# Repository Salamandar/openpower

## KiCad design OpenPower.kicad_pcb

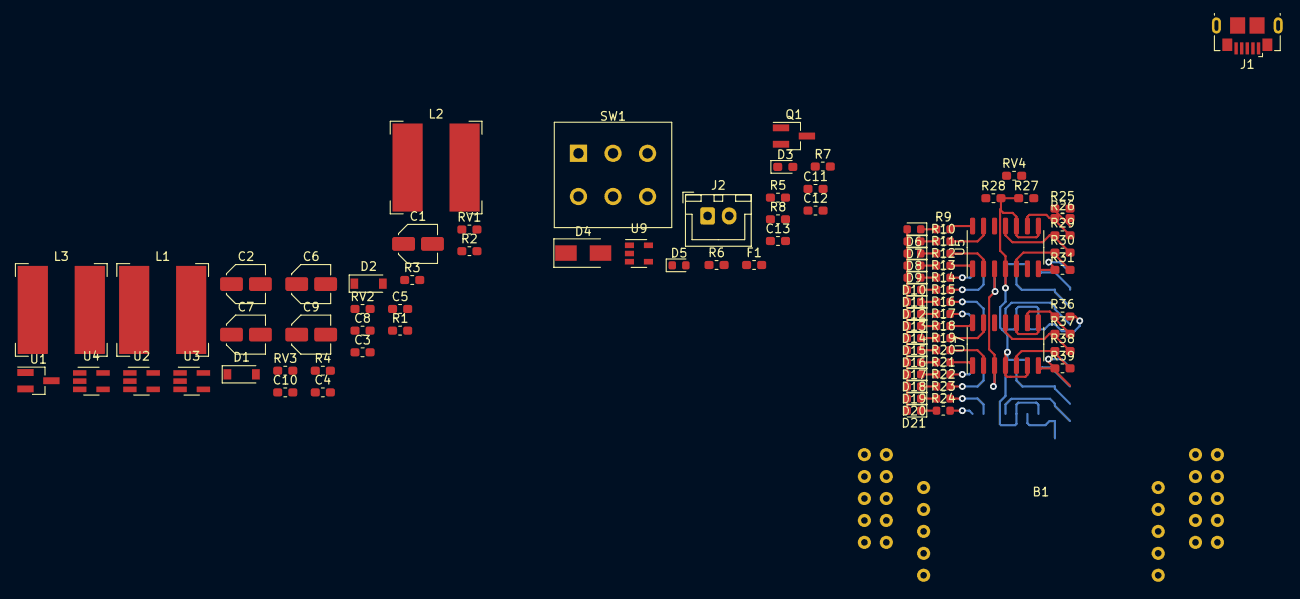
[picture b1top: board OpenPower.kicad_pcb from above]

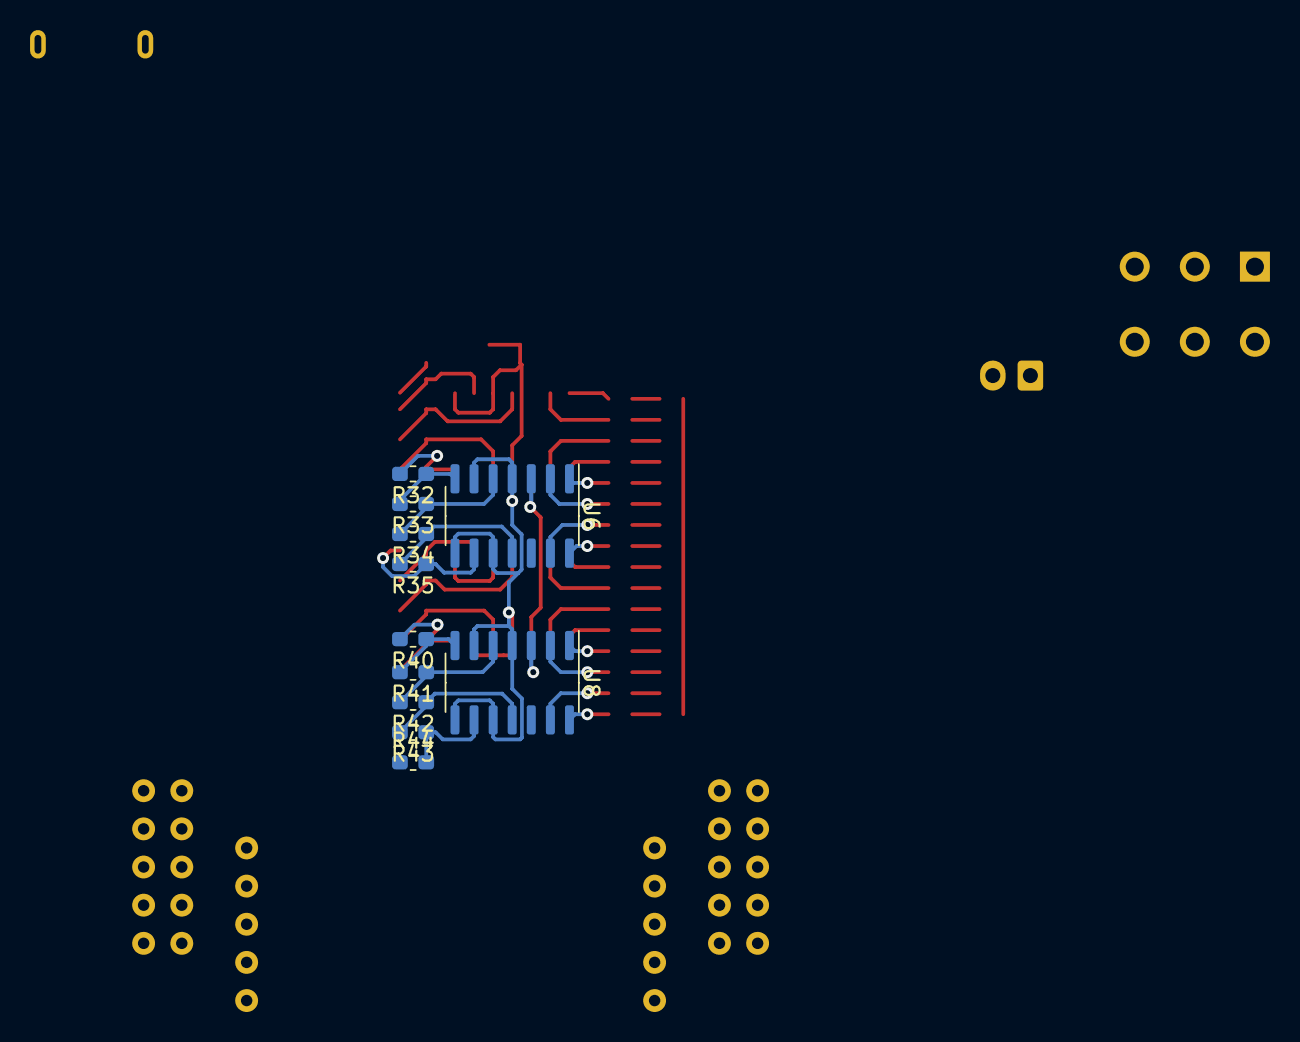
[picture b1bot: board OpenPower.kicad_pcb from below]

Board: 2 copper layers, 100 parts (11 on the bottom side), 69 nets.

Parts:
B1: breadboard
C1, C2, C6, C7: 22u; C_Elec_4x5.8
C3, C4, C8, C13: 1u; C_0603_1608Metric_Pad1.05x0.95mm_HandSolder
C5: 5.6u; C_0603_1608Metric_Pad1.05x0.95mm_HandSolder
C9: 100u; C_Elec_4x5.8
C10: 2u2; C_0603_1608Metric_Pad1.05x0.95mm_HandSolder
C11, C12: 4u7; C_0603_1608Metric_Pad1.05x0.95mm_HandSolder
D1, D2: D_Schottky; D_SOD-123
D3: LED; LED_0603_1608Metric_Pad1.05x0.95mm_HandSolder
D4: B130LAW; D_SMA
D5, D6, D7, D8, D9, D10, D11, D12, D13, D14, D15, D16, D17, D18, D19, D20, D21: LED; LED_0603_1608Metric
F1: Fuse; Fuse_0603_1608Metric_Pad1.05x0.95mm_HandSolder
J1: USB_B_Micro; USB_Micro-B_GCT_USB3076-30-A
J2: Battery; JST_XH_B2B-XH-A_1x02_P2.50mm_Vertical
L1, L2, L3: 22uH; L_Bourns-SRN1060
Q1: PMOS; SOT-23_Handsoldering
R1, R7: 100k; R_0603_1608Metric_Pad1.05x0.95mm_HandSolder
R2, R25: 12k; R_0603_1608Metric_Pad1.05x0.95mm_HandSolder
R3: 82k; R_0603_1608Metric_Pad1.05x0.95mm_HandSolder
R4: 2k2; R_0603_1608Metric_Pad1.05x0.95mm_HandSolder
R5, R27, R28, R29, R30, R31, R32, R33, R34, R35, R36, R40: 10k; R_0603_1608Metric_Pad1.05x0.95mm_HandSolder
R6, R8: 470; R_0603_1608Metric_Pad1.05x0.95mm_HandSolder
R9, R10, R11, R12, R13, R14, R15, R16, R17, R18, R19, R20, R21, R22, R23, R24: 1k; R_0603_1608Metric
R26: 1k; R_0603_1608Metric_Pad1.05x0.95mm_HandSolder
R37, R43: 4k; R_0603_1608Metric_Pad1.05x0.95mm_HandSolder
R38, R39: 3k; R_0603_1608Metric_Pad1.05x0.95mm_HandSolder
R41, R42: 5k; R_0603_1608Metric_Pad1.05x0.95mm_HandSolder
R44: 6k; R_0603_1608Metric_Pad1.05x0.95mm_HandSolder
RV1, RV2, RV3, RV4: 100k; R_0603_1608Metric_Pad1.05x0.95mm_HandSolder
SW1: SW_DPDT_x2; SW_PUSH_E-Switch_FS5700DP_DPDT
U1: XC6206P; SOT-23_Handsoldering
U2, U3: MT3608; SOT-23-5_HandSoldering
U4: MIC5205-5.0YM5; SOT-23-5_HandSoldering
U5, U6, U7, U8: LM339; SOIC-14_3.9x8.7mm_P1.27mm
U9: MCP73831T; SOT-23-5

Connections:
+3V3: B1.10, B1.11, B1.12, B1.13, B1.14, C4.1, D6.2, D7.2, D8.2, D9.2, D10.2, D11.2, D12.2, D13.2, D14.2, D15.2, D16.2, D17.2, D18.2, D19.2, D20.2, D21.2, R25.2, U1.2
+5V: B1.5, B1.6, B1.7, B1.8, B1.9, C10.2, U4.5, U5.3, U6.3, U7.3, U8.3
+BATT: C12.1, J2.1, Q1.1, U9.3
/Vinput[3.5-5.5V]: C1.1, C2.1, C3.1, L1.1, L2.1, R8.2, SW1.1, SW1.4, U1.3, U2.4, U2.5, U3.4, U3.5
/voltage_meter/Vcompare: R27.1, R28.2, RV4.2, U5.4, U5.6, U5.8, U5.10, U6.4, U6.6, U6.8, U6.10, U7.4, U7.6, U7.8, U7.10, U8.4, U8.6, U8.8, U8.10
GND: B1.2, B1.4, C1.2, C2.2, C3.2, C4.2, C6.1, C7.1, C8.1, C9.1, C10.1, C11.2, C12.2, C13.2, D5.1, J1.5, J1.6, J2.2, L3.2, R2.1, R4.1, R5.2, R7.1, R28.1, R44.1, RV3.1, RV4.1, U1.1, U2.2, U3.2, U4.2, U5.12, U6.12, U7.12, U8.12, U9.2
unnamed: C5.1, D2.2, L3.1
unnamed: C5.2, L2.2, U3.1
unnamed: C6.2, C8.2, D1.1, R1.2, U4.1, U4.3
unnamed: C13.1, D4.1, Q1.3, SW1.2, SW1.3, SW1.5, SW1.6
unnamed: D1.2, L1.2, U2.1
unnamed: D3.1, U9.1
unnamed: D3.2, R6.1
unnamed: D5.2, R8.1
unnamed: D6.1, R9.1
unnamed: D7.1, R10.1
unnamed: D8.1, R11.1
unnamed: D9.1, R12.1
unnamed: D10.1, R13.1
unnamed: D11.1, R14.1
unnamed: D12.1, R15.1
unnamed: D13.1, R16.1
unnamed: D14.1, R17.1
unnamed: D15.1, R18.1
unnamed: D16.1, R19.1
unnamed: D17.1, R20.1
unnamed: D18.1, R21.1
unnamed: D19.1, R22.1
unnamed: D20.1, R23.1
unnamed: D21.1, R24.1
unnamed: F1.2, J1.1
unnamed: R1.1, R2.2, U2.3
unnamed: R3.1, R4.2, RV1.1, RV2.1, RV2.2, RV3.2, U3.3
unnamed: R5.1, U9.5
unnamed: R9.2, U5.14
unnamed: R10.2, U5.13
unnamed: R11.2, U5.2
unnamed: R12.2, U5.1
unnamed: R13.2, U6.1
unnamed: R14.2, U6.2
unnamed: R15.2, U6.13
unnamed: R16.2, U6.14
unnamed: R17.2, U7.14
unnamed: R18.2, U7.13
unnamed: R19.2, U7.2
unnamed: R20.2, U7.1
unnamed: R21.2, U8.1
unnamed: R22.2, U8.2
unnamed: R23.2, U8.13
unnamed: R24.2, U8.14
unnamed: R25.1, R26.2
unnamed: R26.1, R29.2, U5.9
unnamed: R29.1, R30.2, U5.11
unnamed: R30.1, R31.2, U5.5
unnamed: R31.1, R32.2, U5.7
unnamed: R32.1, R33.2, U6.7
unnamed: R33.1, R34.2, U6.5
unnamed: R34.1, R35.2, U6.11
unnamed: R35.1, R36.2, U6.9
unnamed: R36.1, R37.2, U7.9
unnamed: R37.1, R38.2, U7.11
unnamed: R38.1, R39.2, U7.5
unnamed: R39.1, R40.2, U7.7
unnamed: R40.1, R41.2, U8.7
unnamed: R41.1, R42.2, U8.5
unnamed: R42.1, R43.2, U8.11
unnamed: R43.1, R44.2, U8.9
VBUS: C11.1, D4.2, F1.1, Q1.2, R6.2, R7.2, U9.4
VCC: B1.1, B1.3, C7.2, C9.2, D2.1, R3.2, R27.2, RV1.2

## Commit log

2019-08-27 initial commit, shematics finished
2019-08-28 finish schematics, started pcb
